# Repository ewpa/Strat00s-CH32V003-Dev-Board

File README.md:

# CH32V003-Dev-Board

A minimal CH32V003F4U6 based dev board for playing with the CH32V003 MCU.

The board should have everything required to get the chip working, together with a ME6211C33M5 3v LDO. The LDO is not required and can be ommited, but LEDs won't work as they are powered from it. The 3V and 5V rails can be joined together to power them again. USB is wired to hopefully support [RV003USB](https://github.com/cnlohr/rv003usb) bootloader.

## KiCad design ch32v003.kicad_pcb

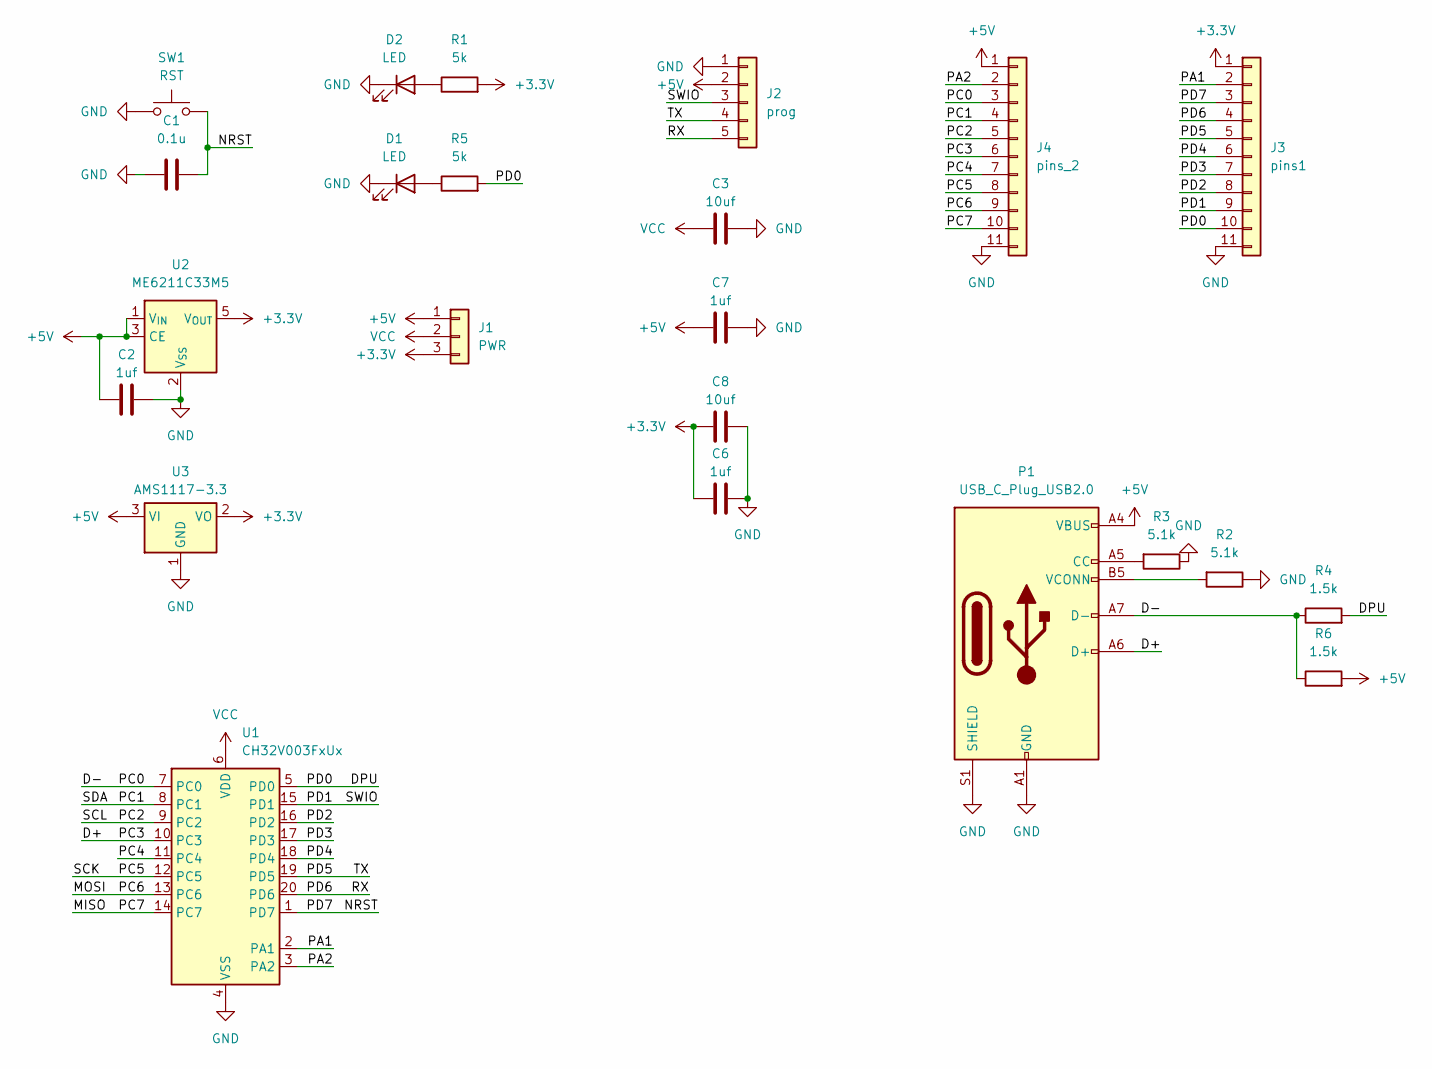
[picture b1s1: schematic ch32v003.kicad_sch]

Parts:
C1: 0.1u; C_0603_1608Metric
C2, C6, C7: 1uf; C_0603_1608Metric
C3, C8: 10uf; C_0603_1608Metric
D1, D2: LED; LED_0603_1608Metric
J1: PWR; SolderJumper-3_P1.3mm_Open_Pad1.0x1.5mm
J2: prog; PinHeader_1x05_P2.54mm_Vertical
J3: pins1; PinHeader_1x11_P2.54mm_Vertical
J4: pins_2; PinHeader_1x11_P2.54mm_Vertical
P1: USB_C_Plug_USB2.0; USB_C_Receptacle_HRO_TYPE-C-31-M-12
R1, R5: 5k; R_0603_1608Metric
R2, R3: 5.1k; R_0603_1608Metric
R4, R6: 1.5k; R_0603_1608Metric
SW1: RST; SW_Push_SPST_NO_Alps_SKRK
U1: CH32V003FxUx; QFN-20-1EP_3x3mm_P0.4mm_EP1.65x1.65mm
U2: ME6211C33M5; SOT-23-5
U3: AMS1117-3.3; SOT-223-3_TabPin2

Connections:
+3.3V: C6.1, C8.1, J1.3, J3.1, R1.2, U2.5 (V_{OUT}), U3.2 (VO)
+5V: C2.1, C7.1, J1.1, J2.2, J4.1, P1.A4 (VBUS), P1.A9 (VBUS), P1.B4 (VBUS), P1.B9 (VBUS), R6.2, U2.1 (V_{IN}), U2.3 (CE), U3.3 (VI)
/D+: J4.6, P1.A6 (D+), U1.10 (PC3)
/D-: J4.3, P1.A7 (D-), R4.1, R6.1, U1.7 (PC0)
/DPU: J3.10, R4.2, R5.2, U1.5 (PD0)
/MISO: J4.10, U1.14 (PC7)
/MOSI: J4.9, U1.13 (PC6)
/NRST: C1.2, J3.3, SW1.2, U1.1 (PD7)
/PA1: J3.2, U1.2 (PA1)
/PA2: J4.2, U1.3 (PA2)
/PC1: J4.4, U1.8 (PC1)
/PC2: J4.5, U1.9 (PC2)
/PC4: J4.7, U1.11 (PC4)
/PC5: J4.8, U1.12 (PC5)
/PD1: J2.3, J3.9, U1.15 (PD1)
/PD2: J3.8, U1.16 (PD2)
/PD3: J3.7, U1.17 (PD3)
/PD4: J3.6, U1.18 (PD4)
/PD5: J2.4, J3.5, U1.19 (PD5)
/PD6: J2.5, J3.4, U1.20 (PD6)
GND: C1.1, C2.2, C3.2, C6.2, C7.2, C8.2, D1.1 (K), D2.1 (K), J2.1, J3.11, J4.11, P1.A1 (GND), P1.A12 (GND), P1.B1 (GND), P1.B12 (GND), P1.S1 (SHIELD), R2.1, R3.1, SW1.1, U1.4 (VSS), U1.21 (VSS), U2.2 (V_{SS}), U3.1 (GND)
unnamed: D1.2 (A), R5.1
unnamed: D2.2 (A), R1.1
unnamed: P1.A5 (CC), R3.2
unnamed: P1.B5 (VCONN), R2.2
VCC: C3.1, J1.2, U1.6 (VDD)

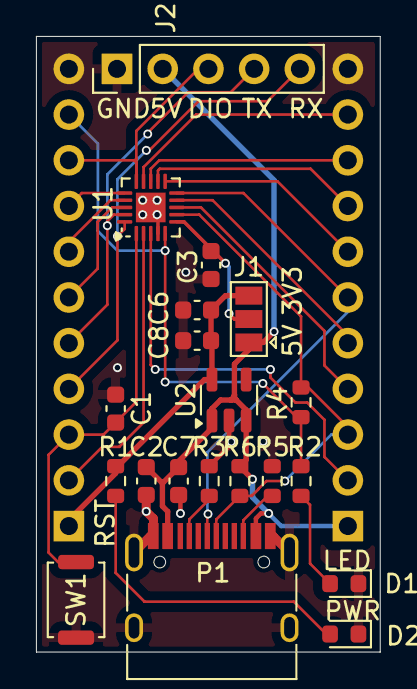
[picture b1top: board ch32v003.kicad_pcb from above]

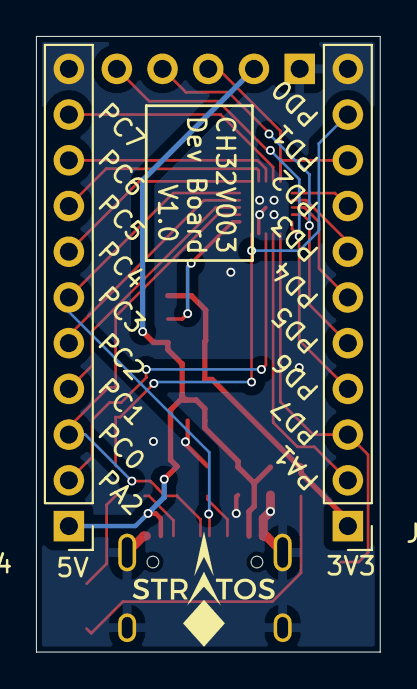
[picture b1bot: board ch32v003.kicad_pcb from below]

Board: 2 copper layers, 19.1 x 34.2 mm, 22 parts (2 on the bottom side), 26 nets.

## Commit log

2024-05-21 Add missing 3d models
2024-05-21 board renders
2024-08-17 Change missing typeface.
2024-08-17 Tidy up fabrication layer.
